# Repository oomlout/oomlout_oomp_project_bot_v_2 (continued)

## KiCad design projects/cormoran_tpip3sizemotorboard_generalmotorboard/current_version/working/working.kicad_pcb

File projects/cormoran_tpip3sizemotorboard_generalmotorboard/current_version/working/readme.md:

# tpip3sizemotorboard
 
## summary 
* id: cormoran_tpip3sizemotorboard_generalmotorboard
* user: cormoran
* name: tpip3sizemotorboard
* board: generalmotorboard
* repo: https://github.com/cormoran/TPIP3SizeMotorBoard
* src_file_repo_kicad_pcb: hardware/generalmotorboard.kicad_pcb
* src_file_repo_kicad_pcb_link: https://github.com/cormoran/TPIP3SizeMotorBoard/tree/master/hardware/generalmotorboard.kicad_pcb

* src_file_repo_sch: hardware/generalmotorboard.sch
* src_file_repo_sch_link: https://github.com/cormoran/TPIP3SizeMotorBoard/tree/master/hardware/generalmotorboard.sch
* full details link: https://github.com/oomlout/oomlout_oomp_project_bot_v_2/tree/main/projects/cormoran_tpip3sizemotorboard_generalmotorboard/current_version/working

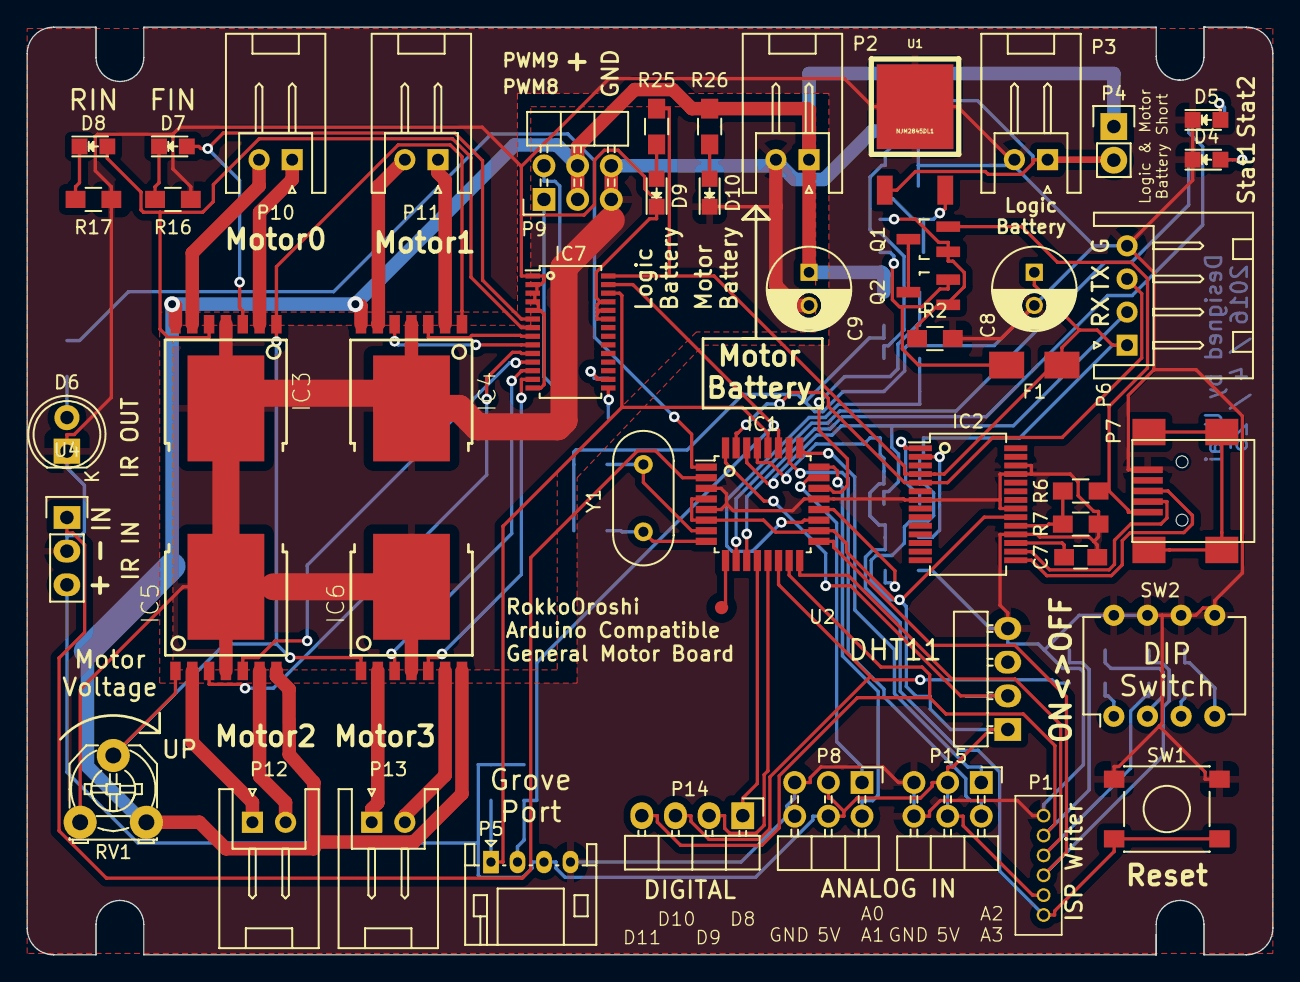
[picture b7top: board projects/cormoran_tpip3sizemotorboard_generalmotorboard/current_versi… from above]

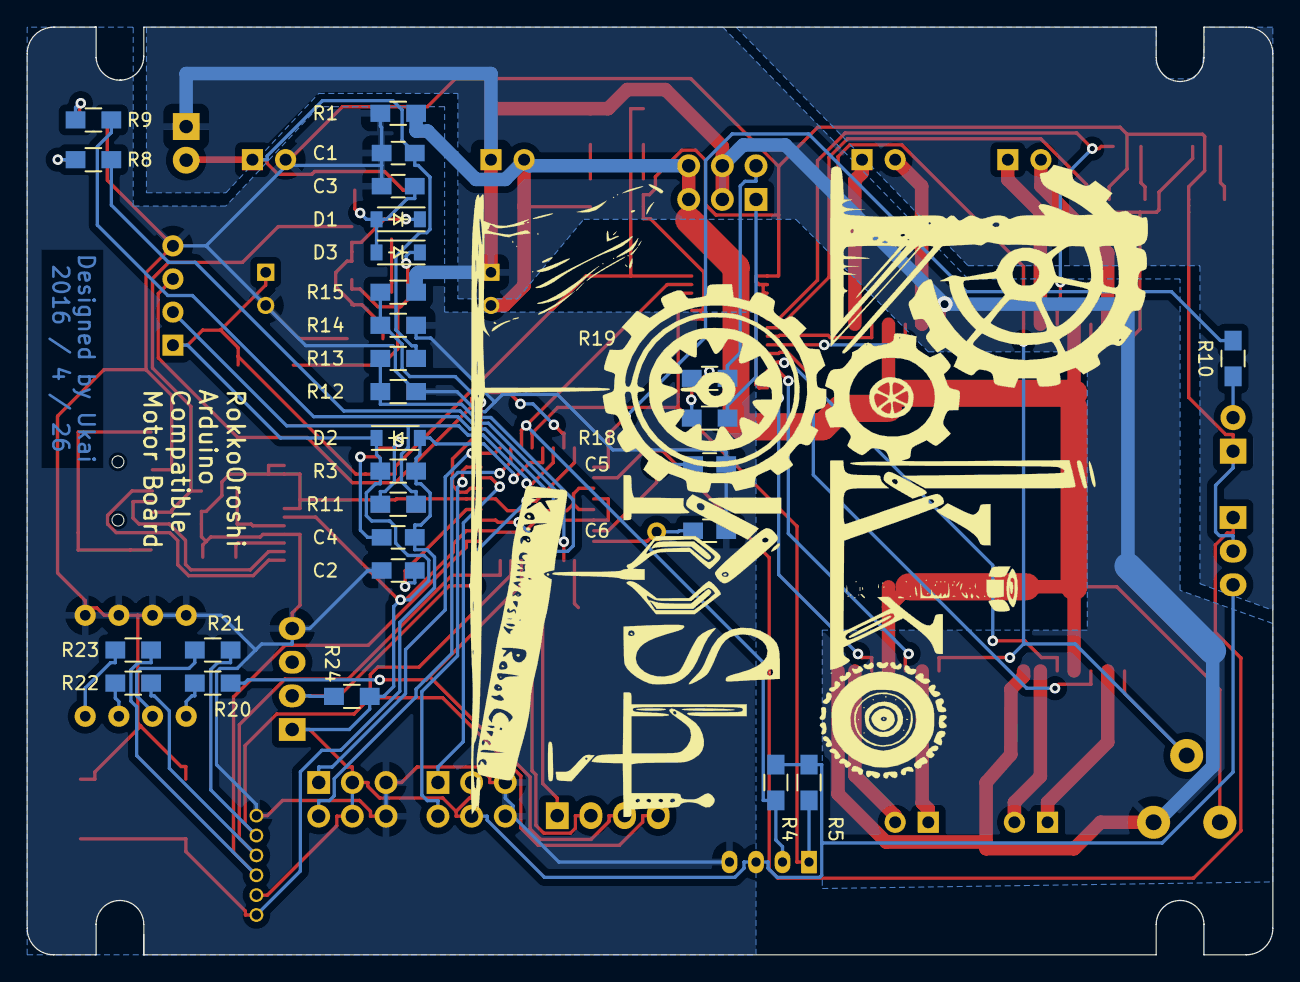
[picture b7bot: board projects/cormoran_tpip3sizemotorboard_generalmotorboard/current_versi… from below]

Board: 2 copper layers, 94.0 x 70.0 mm, 78 parts (28 on the bottom side), 74 nets.

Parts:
C1: 0.33uF; C_0805_HandSoldering
C2, C7: 100nF; C_0805_HandSoldering
C3: 2.2uF; C_0805_HandSoldering
C4: 0.1uF; C_0805_HandSoldering
C5, C6: 22pF; C_0805_HandSoldering
C8, C9: 470uF; C_Radial_D6.3_L11.2_P2.5
D1, D2, D3: D; SOD-123
D4: LED GREEN; LED_0805
D5: LED RED; LED_0805
D6: LED IR; LED-5MM
D7: Led FIN; LED_0805
D8: Led RIN; LED_0805
D9: Led MBAT; LED_0805
D10: Led LBAT; LED_0805
F1: 500mA; Fuse_SMD1206_HandSoldering
IC1: ATMEGA328P-A; TQFP-32_7x7mm_Pitch0.8mm
IC2: FT232RL; SSOP-28_5.3x10.2mm_Pitch0.65mm
IC3, IC4, IC5, IC6: BD6222HFP; HRP7
IC7: PCA9685_TSSOP-28_4MM; TSSOP-28_4.4x9.7mm_Pitch0.65mm
P1: ISP Writer; B6B-ZR
P2: MOTOR-BAT; JST_XH_S2B-XH-A_02x2.50mm_Angled
P3: LOGIC-BAT; JST_XH_S2B-XH-A_02x2.50mm_Angled
P4: JUMP; Pin_Header_Straight_1x02
P5: Grove; JST_PH_S4B-PH-K_04x2.00mm_Angled
P6: Serial; JST_XH_S4B-XH-A_04x2.50mm_Angled
P7: USB_OTG; USB_Mini-B
P8, P15: IO; Pin_Header_Angled_2x03_without_pin_show
P9: SERVO; Pin_Header_Angled_2x03_without_pin_show
P10: Motor1; JST_XH_S2B-XH-A_02x2.50mm_Angled
P11: Motor2; JST_XH_S2B-XH-A_02x2.50mm_Angled
P12: Motor3; JST_XH_S2B-XH-A_02x2.50mm_Angled
P13: Motor4; JST_XH_S2B-XH-A_02x2.50mm_Angled
P14: IO; Pin_Header_Angled_1x04_without_pin_show
P16: IOPAD; Fiducial_Mark
Q1, Q2: Q_PMOS_GSD; SOT-23_Handsoldering
R1: 0; R_0805_HandSoldering
R2, R3, R7, R13, R15, R24: 10k; R_0805_HandSoldering
R4, R5, R6, R20, R21, R22, R23: 4.7k; R_0805_HandSoldering
R8, R9, R16, R17, R25, R26: 470; R_0805_HandSoldering
R10, R18, R19: 330; R_0805_HandSoldering
R11: 1k; R_0805_HandSoldering
R12: 20k; R_0805_HandSoldering
R14: 30k; R_0805_HandSoldering
RV1: 10k; Potentiometer_Triwood_RM-065
SW1: SW_PUSH; SW_SPST_PTS645
SW2: SETTING; DIP-8_W7.62mm
U1: NJM2845DL1; TO-252-3
U2: DHT11
U4: IR_Receiver; Pin_Header_Straight_1x03
Y1: 16MHz; HC-49V

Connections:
5VBATSENS: IC1.19, R12.2, R13.1
8VBATSENS: IC1.22, R14.2, R15.1
+5V: C8.1, D2.1, F1.2, IC1.4, IC1.6, IC1.18, IC2.4, IC2.20, IC7.28, P1.2, P5.3, P6.1, P8.3, P8.4, P15.3, P15.4, R3.1, R4.1, R5.1, R24.1, R25.2, U2.1, U4.3
+8V: C9.1, IC3.7, IC4.7, IC5.7, IC6.7, P2.1, P4.1, P9.3, P9.4, R14.1, R26.2, RV1.3
A0: IC1.23, P8.1
A1: IC1.24, P8.2
A2: IC1.25, P15.1
A3: IC1.26, P15.2
BATTERY: C1.1, P3.1, P4.2, R12.1, U1.1
D8: IC1.12, P14.1
D9: IC1.13, P14.2
D10: IC1.14, P14.3, R20.1
D11: IC1.15, P1.5, P14.4, R21.1
DTR: C4.2, IC2.2
GND: C9.2, D10.1, IC3.4, IC3.P, IC4.4, IC4.P, IC5.4, IC5.P, IC6.4, IC6.P, P2.2, P9.5, P9.6, R1.1, RV1.1
GNDD: C1.2, C2.2, C3.2, C5.1, C6.1, C7.2, C8.2, D4.1, D5.1, D6.1, D9.1, IC1.3, IC1.5, IC1.21, IC2.7, IC2.18, IC2.21, IC2.25, IC2.26, IC7.1, IC7.2, IC7.3, IC7.4, IC7.5, IC7.14, IC7.23, IC7.24, IC7.25, P1.6, P3.2, P5.4, P6.4, P7.5, P8.5, P8.6, P15.5, P15.6, R1.2, R2.2, R7.2, R13.2, R15.2, R16.1, R17.1, SW1.1, SW2.5, SW2.6, SW2.7, SW2.8, U1.2, U2.4, U4.2
IR-RCV: IC1.2, U4.1
IRLED: IC1.1, R10.2
MISO: IC1.16, P1.4, R22.1
unnamed: C2.1, IC1.20
unnamed: C3.1, D1.2, D3.2, U1.3
unnamed: C5.2, IC1.7, Y1.1
unnamed: C6.2, IC1.8, Y1.2
unnamed: C7.1, IC2.17
unnamed: D1.1, Q1.1, Q2.1, R2.1
unnamed: D3.1, F1.1, Q2.2
unnamed: D4.2, R8.1
unnamed: D5.2, R9.1
unnamed: D6.2, R10.1
unnamed: D7.1, R16.2
unnamed: D7.2, IC3.3, IC7.6
unnamed: D8.1, R17.2
unnamed: D8.2, IC3.5, IC7.7
unnamed: D9.2, R25.1
unnamed: D10.2, R26.1
unnamed: IC1.9, P16.1
unnamed: IC2.1, R11.2
unnamed: IC2.15, P7.3
unnamed: IC2.16, P7.2
unnamed: IC2.19, R6.1, R7.1
unnamed: IC3.1, IC4.1, IC5.1, IC6.1, RV1.2
unnamed: IC3.2, P10.1
unnamed: IC3.6, P10.2
unnamed: IC4.2, P11.1
unnamed: IC4.3, IC7.8
unnamed: IC4.5, IC7.9
unnamed: IC4.6, P11.2
unnamed: IC5.2, P12.1
unnamed: IC5.3, IC7.10
unnamed: IC5.5, IC7.11
unnamed: IC5.6, P12.2
unnamed: IC6.2, P13.1
unnamed: IC6.3, IC7.12
unnamed: IC6.5, IC7.13
unnamed: IC6.6, P13.2
unnamed: P9.1, R18.1
unnamed: P9.2, R19.1
unnamed: Q1.3, Q2.3
unnamed: R20.2, SW2.1
unnamed: R21.2, SW2.2
unnamed: R22.2, SW2.3
unnamed: R23.2, SW2.4
PWM8: IC7.15, R18.2
PWM9: IC7.16, R19.2
RESET: C4.1, D2.2, IC1.29, P1.1, R3.2, SW1.2
RX: IC1.30, P6.2, R11.1
SCK: IC1.17, P1.3, R23.1
SCL: IC1.28, IC7.26, P5.1, R5.2
SDA: IC1.27, IC7.27, P5.2, R4.2
STAT1: IC1.10, R8.2
STAT2: IC1.11, R9.2
TEMP_SENSOR: IC1.32, R24.2, U2.2
TX: IC1.31, IC2.5, P6.3
USBVCC: P7.1, Q1.2, R6.2
